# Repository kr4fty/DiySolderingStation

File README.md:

# Soldering Station 

Diy Estación de soldado con Atmega328 (Arduino UNO), compatible con HAKKO 936/937/928/926

## Información

Estacion de soldado hecho sobre un Atmega328, utilizando un Lapiz de una estación Hakko.

A diferencia de la estación original, esta alimenta a la Punta/Lapíz con corriente alterna (CA, 24Vac).

ATENCIÓN: Tener en cuenta que este Lapiz utiliza un PTC para el sensado de la temperatura y NO una termocupla.

<p align="center">
  <br><br>
  <b>Lapiz utilizado</b><br>
  
  <br>
</p>

## Caracteristicas

  * ESD, Antiestático
  * Tensión: 24 Vac 
  * Rango de temperaturas: 120-480 ºC.
  * Potencia: 50 W

## Partes

  * LCD del tipo I²C: se utilizó un lcd de un Motorola C115 (chipset ST7558)
  * Encoder rotatorio para chasis
  * Punta/lapiz de Estación de soldado, compatible con HAKKO 907 (DIN 5 ESD)
  * Botón para chasis
  * Controlador (incluido en el repositorio)

## Software

Depende de las librerias:
  * [ArduinoPID](https://github.com/br3ttb/Arduino-PID-Library): Librería para el control de la temperatura por medio de un PID
  * [ST7558](https://github.com/kr4fty/ST7558-Motorola-C115-LCD-Library): Driver para manejar el LCD
  * [TimerOne](https://github.com/PaulStoffregen/TimerOne): para el Control de Fase de la tensión de alimentación
  * [EnableInterrupt](https://github.com/GreyGnome/EnableInterrupt): Para habilitar tanto las interrupciones externas como las del tipo Pin-Change
  * [EncoderPCI](https://github.com/kr4fty/EncoderPCI): Se encarga de manejar el Encoder

## Hardware

<p align="center">
  <br><br>
  <b>Circuito eléctrico</b><br>
  
  <br>
</p>

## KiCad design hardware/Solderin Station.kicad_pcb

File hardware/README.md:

## About

Created with KiCAD 4.0.6

Tapia Favio

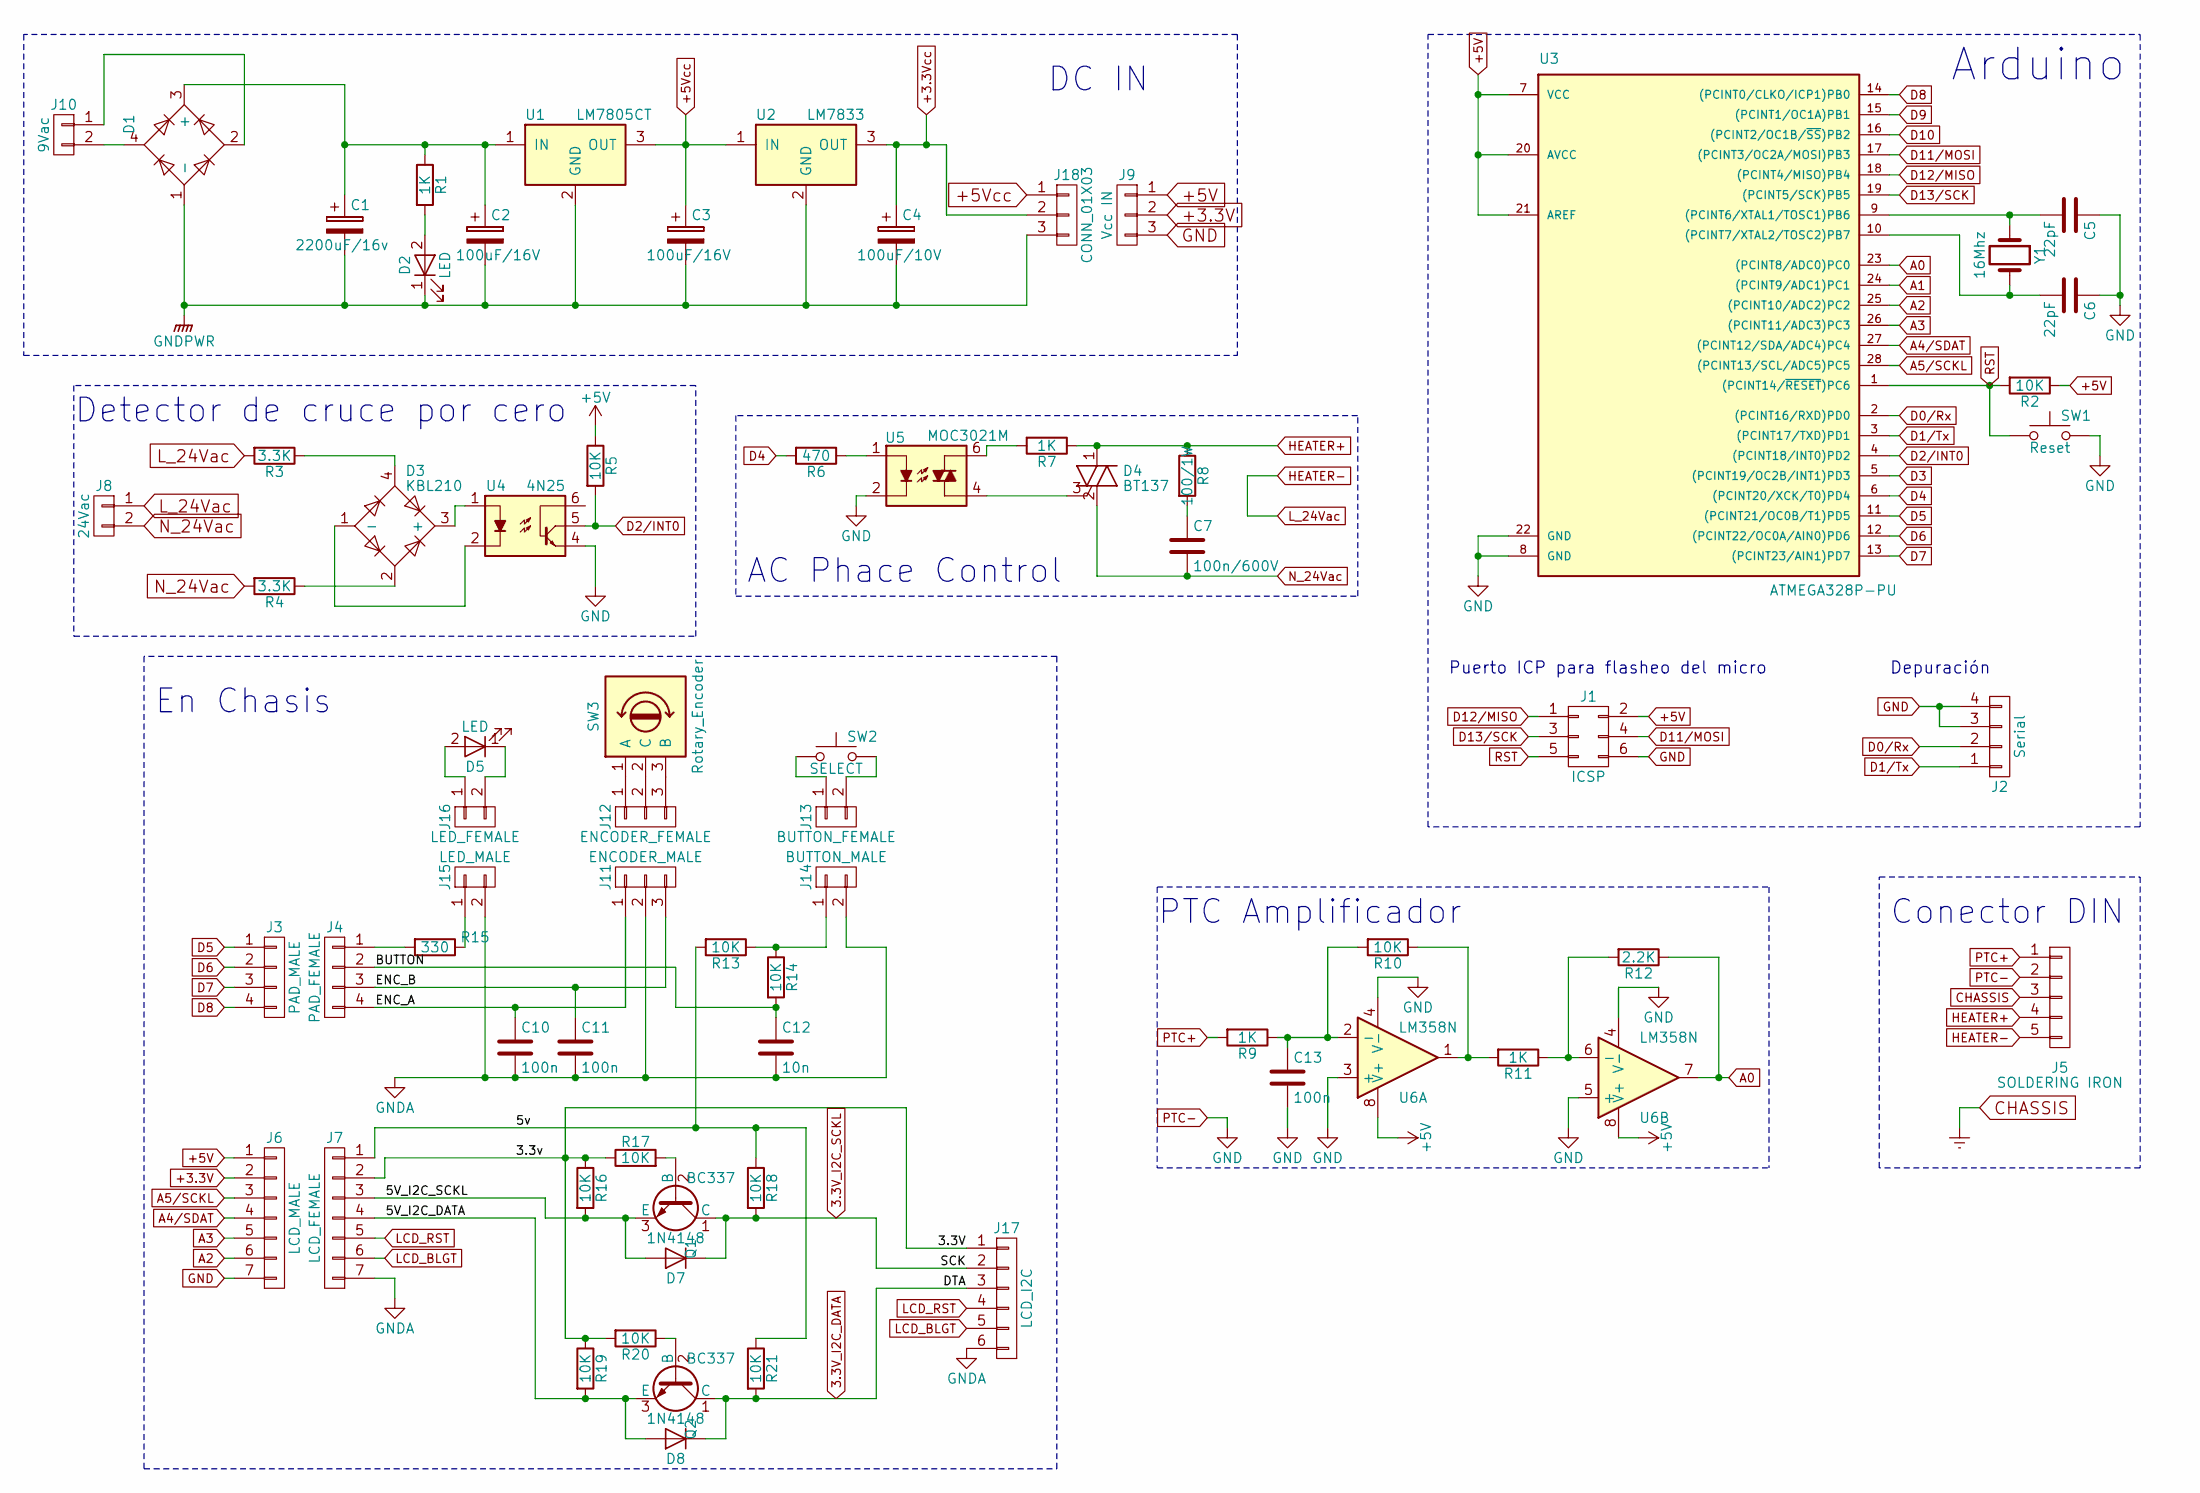
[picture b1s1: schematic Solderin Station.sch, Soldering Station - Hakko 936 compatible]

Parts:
C1: 2200uF/16v; CP_Radial_D12.5mm_P5.00mm
C2, C3: 100uF/16V; CP_Radial_D5.0mm_P2.50mm
C4: 100uF/10V; CP_Radial_D5.0mm_P2.50mm
C5, C6: 22pF; C_Disc_D3.8mm_W2.6mm_P2.50mm
C7: 100n/600V; C_Rect_L11.0mm_W3.5mm_P10.00mm_MKT
C10, C11, C13: 100n; C_Disc_D3.8mm_W2.6mm_P2.50mm
C12: 10n; C_Disc_D3.8mm_W2.6mm_P2.50mm
D1: D_Bridge_-A+A; Diode_Bridge_18.5x5.5
D2, D5: LED; LED_D3.0mm
D3: KBL210; Diode_Bridge_18.5x5.5
D4: BT137; TO-220_Vertical
D7, D8: 1N4148; D_DO-35_SOD27_P7.62mm_Horizontal
J1: ICSP; Pin_Header_Straight_2x03_Pitch2.54mm
J2: Serial; Pin_Header_Straight_1x04_Pitch2.54mm
J3: PAD_MALE; Pin_Header_Straight_1x04_Pitch2.54mm
J4: PAD_FEMALE; Pin_Header_Straight_1x04_Pitch2.54mm
J5: SOLDERING IRON; Pin_Header_Straight_1x05_Pitch2.54mm
J6: LCD_MALE; Pin_Header_Straight_1x07_Pitch2.54mm
J7: LCD_FEMALE; Pin_Header_Straight_1x07_Pitch2.54mm
J8: 24Vac; WireConnection_2.50mmDrill_LargePad
J9: Vcc IN; PINHEAD1-3
J10: 9Vac; WireConnection_2.50mmDrill_LargePad
J11: ENCODER_MALE; PINHEAD1-3
J12: ENCODER_FEMALE; PINHEAD1-3
J13: BUTTON_FEMALE; PINHEAD1-2
J14: BUTTON_MALE; PINHEAD1-2
J15: LED_MALE; PINHEAD1-2
J16: LED_FEMALE; PINHEAD1-2
J17: LCD_I2C; PINHEAD1-6
J18: CONN_01X03; Pin_Header_Straight_1x03_Pitch2.54mm
Q1, Q2: BC337; TO-92_Inline_Narrow_Oval
R1: 1K; R_Axial_DIN0207_L6.3mm_D2.5mm_P7.62mm_Horizontal
R2, R5, R13, R14, R18, R21: 10K; R_Axial_DIN0204_L3.6mm_D1.6mm_P5.08mm_Horizontal
R3, R4: 3.3K; R_Axial_DIN0207_L6.3mm_D2.5mm_P7.62mm_Horizontal
R6: 470; R_Axial_DIN0204_L3.6mm_D1.6mm_P5.08mm_Horizontal
R7, R9, R11: 1K; R_Axial_DIN0204_L3.6mm_D1.6mm_P5.08mm_Horizontal
R8: 100/1W; R_Axial_DIN0207_L6.3mm_D2.5mm_P7.62mm_Horizontal
R10, R16, R17, R19, R20: 10K; R_Axial_DIN0204_L3.6mm_D1.6mm_P2.54mm_Vertical
R12: 2.2K; R_Axial_DIN0204_L3.6mm_D1.6mm_P2.54mm_Vertical
R15: 330; R_Axial_DIN0204_L3.6mm_D1.6mm_P5.08mm_Horizontal
SW1: Reset; SW_PUSH_6mm
SW2: SELECT; SW_PUSH_6mm
SW3: Rotary_Encoder; Potentiometer_Bourns_PTV09A-1_Horizontal
U1: LM7805CT; TO-220_Vertical
U2: LM7833; TO-220_Vertical
U3: ATMEGA328P-PU; DIP-28_W7.62mm
U4: 4N25; DIP-6_W7.62mm
U5: MOC3021M; DIP-6_W7.62mm
U6: LM358N; DIP-8_W7.62mm_LongPads
Y1: 16Mhz; Crystal_HC52-6mm_Vertical

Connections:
3.3V_I2C_DATA: D8.1 (K), J17.3, Q2.1 (C), R21.2
3.3V_I2C_SCKL: D7.1 (K), J17.2, Q1.1 (C), R18.2
+3.3V: J6.2, J9.2
+3.3Vcc: C4.1, J18.2, U2.3 (OUT)
+5V: J1.2, J6.1, J9.1, R2.1, R5.1, U3.7 (VCC), U3.20 (AVCC), U3.21 (AREF), U6.8 (V+)
+5Vcc: C3.1, J18.1, U1.3 (OUT), U2.1 (IN)
/3.3V: J7.2, J17.1, R16.1, R17.1, R19.1, R20.2
/5V_I2C_DATA: D8.2 (A), J7.4, Q2.3 (E), R19.2
/5V_I2C_SCKL: D7.2 (A), J7.3, Q1.3 (E), R16.2
/5v: J7.1, R13.2, R18.1, R21.1
/BUTTON: C12.1, J4.2, R14.2
/ENC_A: C10.1, J4.4, J11.1
/ENC_B: C11.1, J4.3, J11.3
A0: R12.1, U3.23 ((PCINT8/ADC0)PC0), U6.7
A1: U3.24 ((PCINT9/ADC1)PC1)
A2: J6.6, U3.25 ((PCINT10/ADC2)PC2)
A3: J6.5, U3.26 ((PCINT11/ADC3)PC3)
A4/SDAT: J6.4, U3.27 ((PCINT12/SDA/ADC4)PC4)
A5/SCKL: J6.3, U3.28 ((PCINT13/SCL/ADC5)PC5)
CHASSIS: J5.3
D0/Rx: J2.2, U3.2 ((PCINT16/RXD)PD0)
D1/Tx: J2.1, U3.3 ((PCINT17/TXD)PD1)
D2/INT0: R5.2, U3.4 ((PCINT18/INT0)PD2), U4.5
D3: U3.5 ((PCINT19/OC2B/INT1)PD3)
D4: R6.2, U3.6 ((PCINT20/XCK/T0)PD4)
D5: J3.1, U3.11 ((PCINT21/OC0B/T1)PD5)
D6: J3.2, U3.12 ((PCINT22/OC0A/AIN0)PD6)
D7: J3.3, U3.13 ((PCINT23/AIN1)PD7)
D8: J3.4, U3.14 ((PCINT0/CLKO/ICP1)PB0)
D9: U3.15 ((PCINT1/OC1A)PB1)
D10: U3.16 ((PCINT2/OC1B/~SS~)PB2)
D11/MOSI: J1.4, U3.17 ((PCINT3/OC2A/MOSI)PB3)
D12/MISO: J1.1, U3.18 ((PCINT4/MISO)PB4)
D13/SCK: J1.3, U3.19 ((PCINT5/SCK)PB5)
GND: C5.1, C6.1, C13.2, J1.6, J2.3, J2.4, J5.2, J6.7, J9.3, SW1.2, U3.8 (GND), U3.22 (GND), U4.4, U5.2, U6.3 (+), U6.4 (V-), U6.5 (+)
GNDA: C10.2, C11.2, C12.2, J7.7, J11.2, J14.2, J15.2, J17.6
GNDPWR: C1.2, C2.2, C3.2, C4.2, D1.1 (-), D2.1 (K), J18.3, U1.2 (GND), U2.2 (GND)
HEATER+: D4.1 (A1), J5.4, R7.1, R8.1
HEATER-: J5.5, J8.1, R3.2
LCD_BLGT: J7.6, J17.5
LCD_RST: J7.5, J17.4
N_24Vac: C7.2, D4.2 (A2), J8.2, R4.2
unnamed: C1.1, C2.1, D1.3 (+), R1.1, U1.1 (IN)
unnamed: C5.2, U3.9 ((PCINT6/XTAL1/TOSC1)PB6), Y1.1
unnamed: C6.2, U3.10 ((PCINT7/XTAL2/TOSC2)PB7), Y1.2
unnamed: C7.1, R8.2
unnamed: C13.1, R9.1, R10.2, U6.2 (-)
unnamed: D1.2, J10.1
unnamed: D1.4, J10.2
unnamed: D2.2 (A), R1.2
unnamed: D3.1 (-), U4.2
unnamed: D3.2, R4.1
unnamed: D3.3 (+), U4.1
unnamed: D3.4, R3.1
unnamed: D4.3 (G), U5.4
unnamed: D5.1 (K), J16.2
unnamed: D5.2 (A), J16.1
unnamed: J4.1, R15.2
unnamed: J12.1, SW3.1 (A)
unnamed: J12.2, SW3.2 (C)
unnamed: J12.3, SW3.3 (B)
unnamed: J13.1, SW2.1
unnamed: J13.2, SW2.2
unnamed: J14.1, R13.1, R14.1
unnamed: J15.1, R15.1
unnamed: Q1.2 (B), R17.2
unnamed: Q2.2 (B), R20.1
unnamed: R6.1, U5.1
unnamed: R7.2, U5.6
unnamed: R10.1, R11.2, U6.1
unnamed: R11.1, R12.2, U6.6 (-)
PTC+: J5.1, R9.2
RST: J1.5, R2.2, SW1.1, U3.1 ((PCINT14/~RESET~)PC6)

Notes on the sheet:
Puerto ICP para flasheo del micro
Depuración
DC IN
En Chasis
Detector de cruce por cero
AC Phace Control
PTC Amplificador
Arduino
Conector DIN

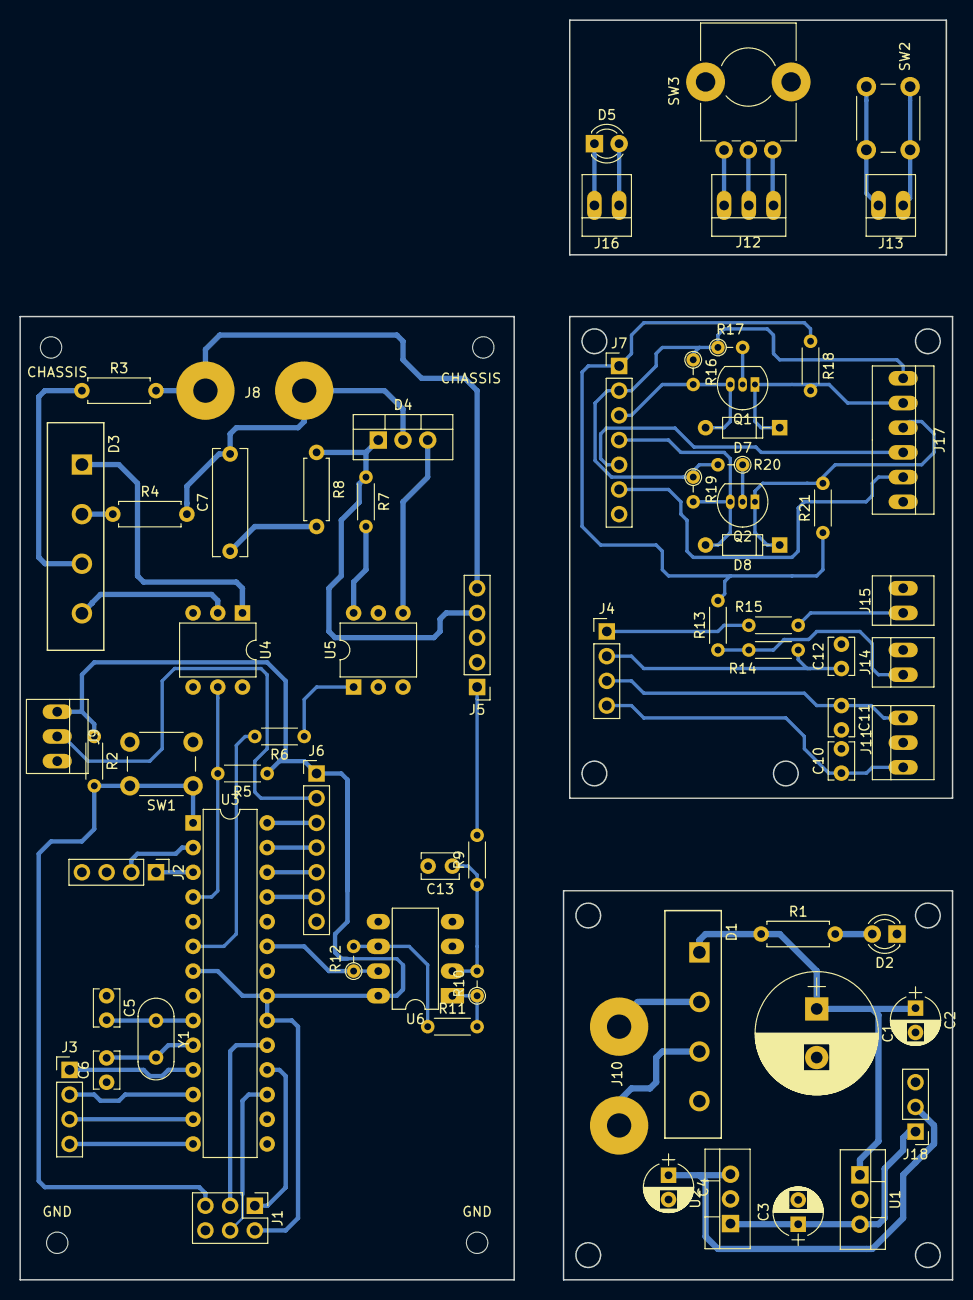
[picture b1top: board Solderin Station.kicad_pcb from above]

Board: 2 copper layers, 95.9 x 129.5 mm, 73 parts (0 on the bottom side), 68 nets.

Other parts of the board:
CHASSIS: MountingHole_2.2mm_M2
CHASSIS#2: MountingHole_2.2mm_M2
GND: MountingHole_2.2mm_M2
GND#2: MountingHole_2.2mm_M2

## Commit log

2017-07-11 update ino
2017-07-12 ptc sensor value
2017-07-13 update firmware
2017-07-13 description is added in the .ino file
